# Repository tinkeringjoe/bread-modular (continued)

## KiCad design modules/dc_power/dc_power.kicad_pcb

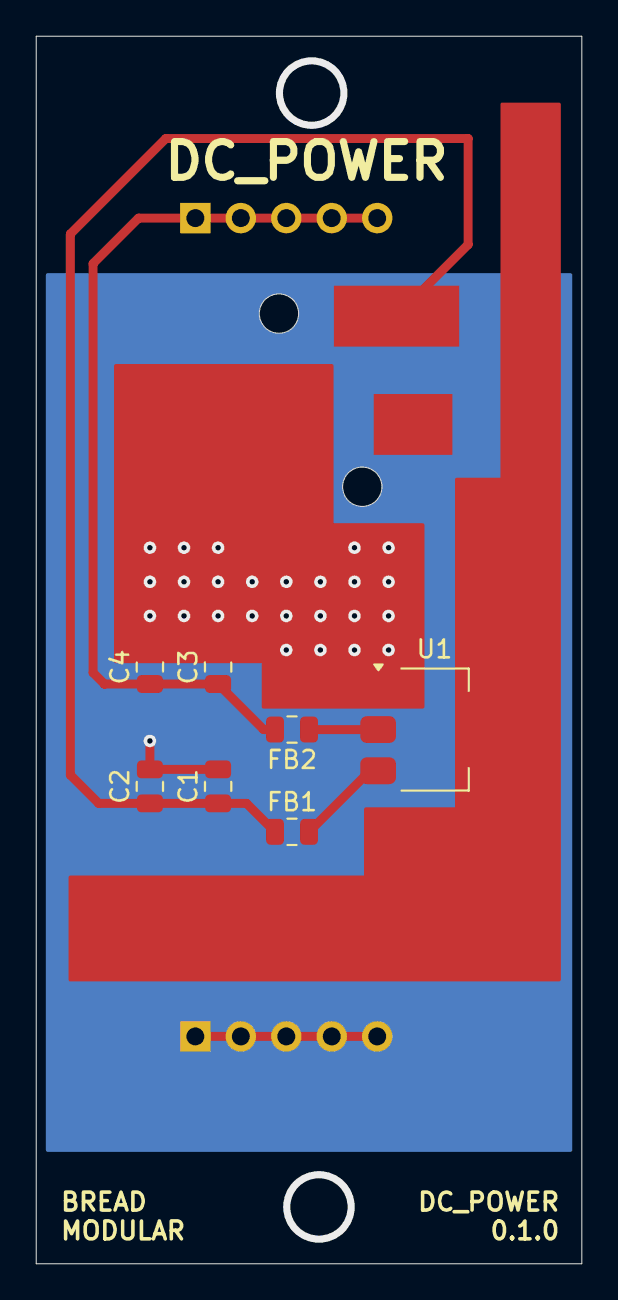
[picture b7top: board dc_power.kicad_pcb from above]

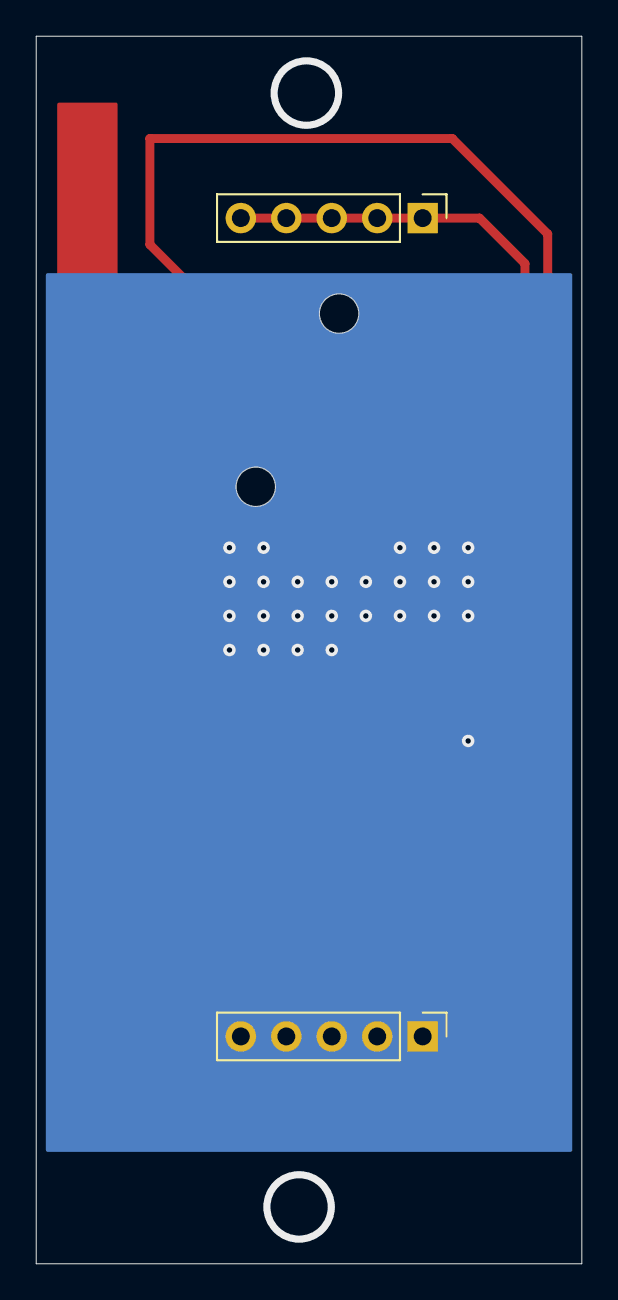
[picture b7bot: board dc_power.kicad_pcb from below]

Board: 2 copper layers, 30.5 x 68.6 mm, 10 parts (2 on the bottom side), 5 nets.

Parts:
5V1: Conn_01x05_Pin; PinHeader_1x05_P2.54mm_Vertical
C1, C3: 10uf; C_0805_2012Metric
C2, C4: 0.1uf; C_0805_2012Metric
FB1, FB2: GZ2012E800TF; C_0805_2012Metric
GND1: Conn_01x05_Pin; PinHeader_1x05_P2.54mm_Vertical
J1: Barrel_Jack_Switch; DC-182-25A
U1: AMS1117-5.0; SOT-223

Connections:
+5V: 5V1.1, 5V1.2, 5V1.3, 5V1.4, 5V1.5, C3.1, C4.1, FB2.2
GND: C1.2, C2.2, C3.2, C4.2, GND1.1, GND1.2, GND1.3, GND1.4, GND1.5, J1.1, U1.1 (GND)
unnamed: C1.1, C2.1, FB1.1, J1.3
unnamed: FB1.2, U1.3 (VI)
unnamed: FB2.1, U1.2 (VO)

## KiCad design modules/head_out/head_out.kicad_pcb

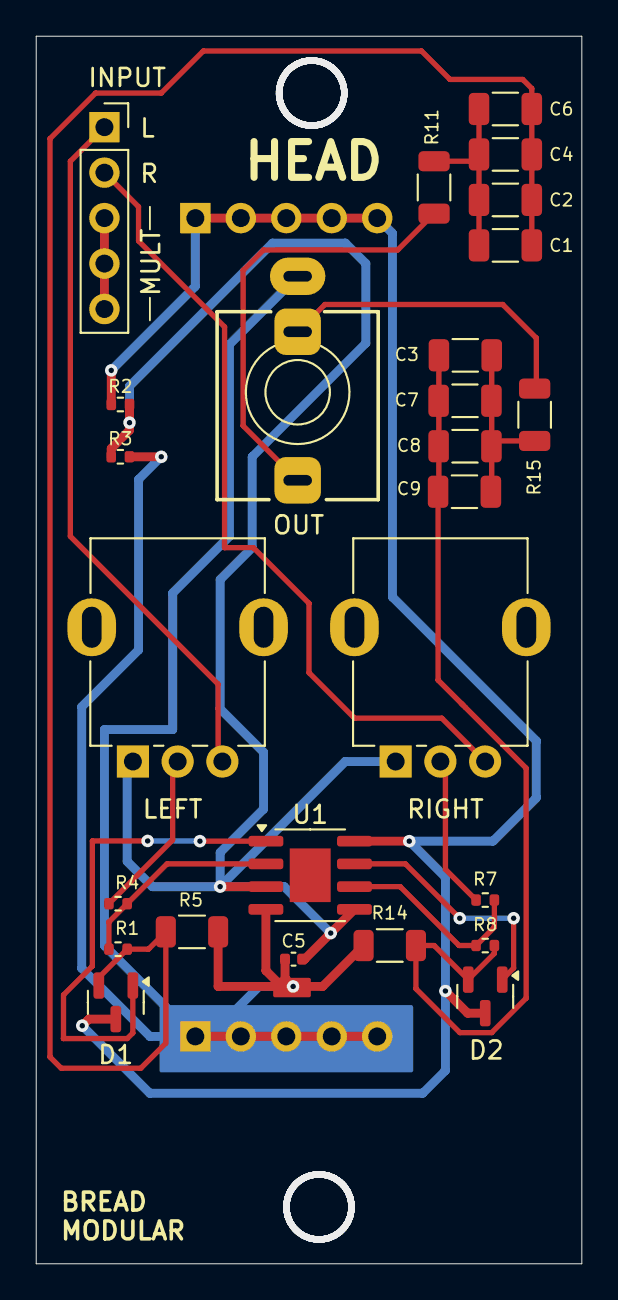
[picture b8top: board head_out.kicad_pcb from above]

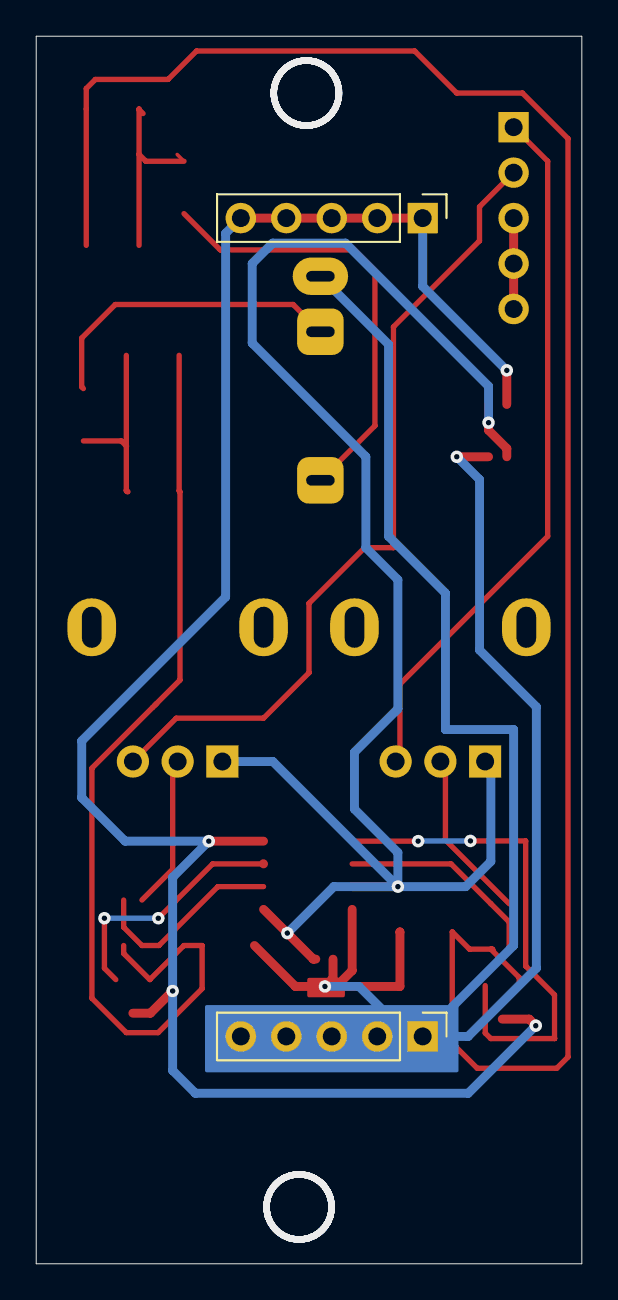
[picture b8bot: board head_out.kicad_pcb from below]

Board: 2 copper layers, 30.5 x 68.6 mm, 28 parts (2 on the bottom side), 18 nets.

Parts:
5V1: Conn_01x05_Pin; PinHeader_1x05_P2.54mm_Vertical
C1, C2, C3, C4, C6, C7, C8, C9: 100uf; C_1206_3216Metric
C5: 0.1uf; C_0402_1005Metric
D1, D2: SS8050; SOT-23
GND1: Conn_01x05_Pin; PinHeader_1x05_P2.54mm_Vertical
INPUT: Conn_01x05_Socket; PinSocket_1x05_P2.54mm_Vertical
LEFT: 50k; Potentiometer_RV09
OUT: AudioJack3; Jack_3.5mm_QingPu_WQP-PJ366ST_Vertical
R1, R8: 22k; R_0402_1005Metric
R2, R3: 1k; R_0402_1005Metric
R4, R7: 100k; R_0402_1005Metric
R5, R14: 100; R_1206_3216Metric
R11, R15: 10; R_1206_3216Metric
RIGHT: 50k; Potentiometer_RV09
U1: MCP6002-xSN; SOIC-8-1EP_3.9x4.9mm_P1.27mm_EP2.29x3mm

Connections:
+2.5V: C5.2, LEFT.1, R2.2, R3.1, RIGHT.1, U1.3 (+), U1.5 (+)
+5V: 5V1.1, 5V1.2, 5V1.3, 5V1.4, 5V1.5, D1.3 (A), D2.3 (A), R2.1, U1.8 (V+)
GND: C5.1, GND1.1, GND1.2, GND1.3, GND1.4, GND1.5, OUT.S, R3.2, R5.1, R14.1, U1.4 (V-)
IN_L: INPUT.1, LEFT.3
IN_R: INPUT.2, RIGHT.3
unnamed: C1.1, C2.1, C4.1, C6.1, D1.2 (K), R1.2, R5.2
unnamed: C1.2, C2.2, C4.2, C6.2, R11.2
unnamed: C3.1, C7.1, C8.1, C9.1, D2.2 (K), R8.2, R14.2
unnamed: C3.2, C7.2, C8.2, C9.2, R15.2
unnamed: D1.1 (K), U1.1
unnamed: D2.1 (K), U1.7
unnamed: INPUT.3, INPUT.4, INPUT.5
unnamed: LEFT.2, R4.1
unnamed: R7.1, RIGHT.2
unnamed: R1.1, R4.2, U1.2 (-)
unnamed: R7.2, R8.1, U1.6 (-)
OUT_L: OUT.T, R11.1
OUT_R: OUT.R, R15.1
